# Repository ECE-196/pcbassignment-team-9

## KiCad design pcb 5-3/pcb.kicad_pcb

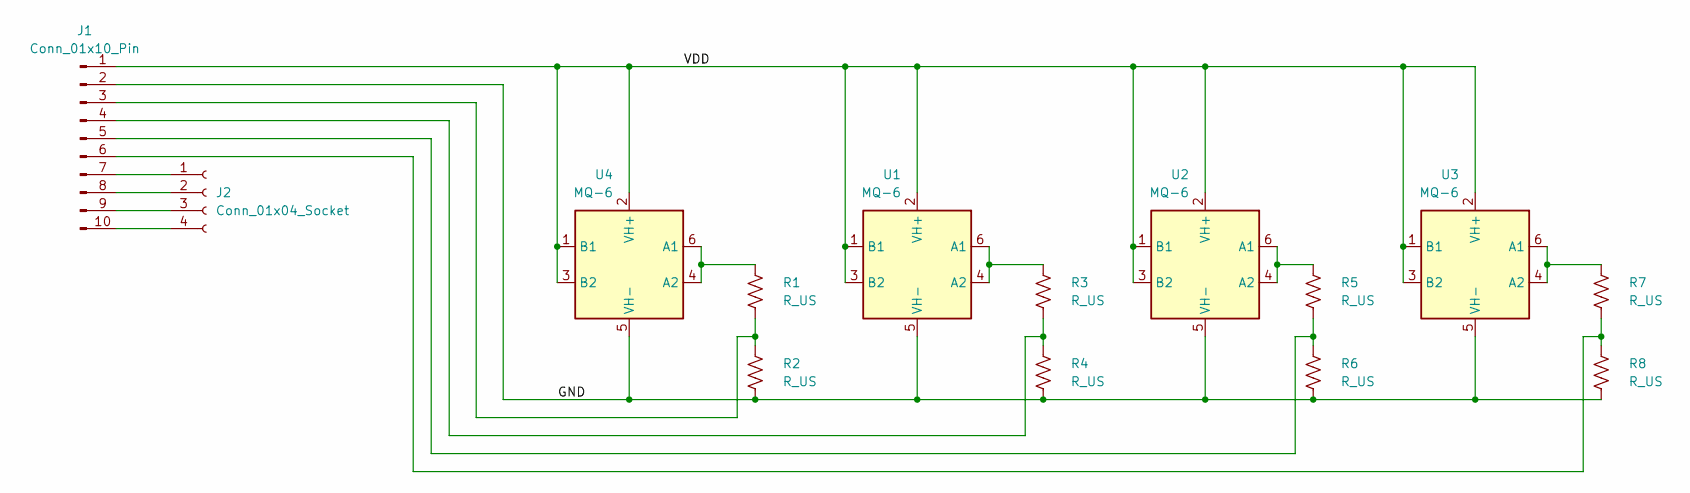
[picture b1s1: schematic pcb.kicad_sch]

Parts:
J1: Conn_01x10_Pin; PinHeader_1x10_P2.54mm_Vertical
J2: Conn_01x04_Socket; PinHeader_1x04_P2.54mm_Vertical
R1, R2, R3, R4, R5, R6, R7, R8: R_US; R_0805_2012Metric
U1, U2, U3, U4: MQ-6

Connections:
/GND: J1.2, R2.2, R4.2, R6.2, R8.2, U1.5 (VH-), U2.5 (VH-), U3.5 (VH-), U4.5 (VH-)
/VDD: J1.1, U1.1 (B1), U1.2 (VH+), U1.3 (B2), U2.1 (B1), U2.2 (VH+), U2.3 (B2), U3.1 (B1), U3.2 (VH+), U3.3 (B2), U4.1 (B1), U4.2 (VH+), U4.3 (B2)
unnamed: J1.3, R1.2, R2.1
unnamed: J1.4, R3.2, R4.1
unnamed: J1.5, R5.2, R6.1
unnamed: J1.6, R7.2, R8.1
unnamed: J1.7, J2.1
unnamed: J1.8, J2.2
unnamed: J1.9, J2.3
unnamed: J1.10, J2.4
unnamed: R3.1, U1.4 (A2), U1.6 (A1)
unnamed: R5.1, U2.4 (A2), U2.6 (A1)
unnamed: R7.1, U3.4 (A2), U3.6 (A1)
unnamed: R1.1, U4.4 (A2), U4.6 (A1)

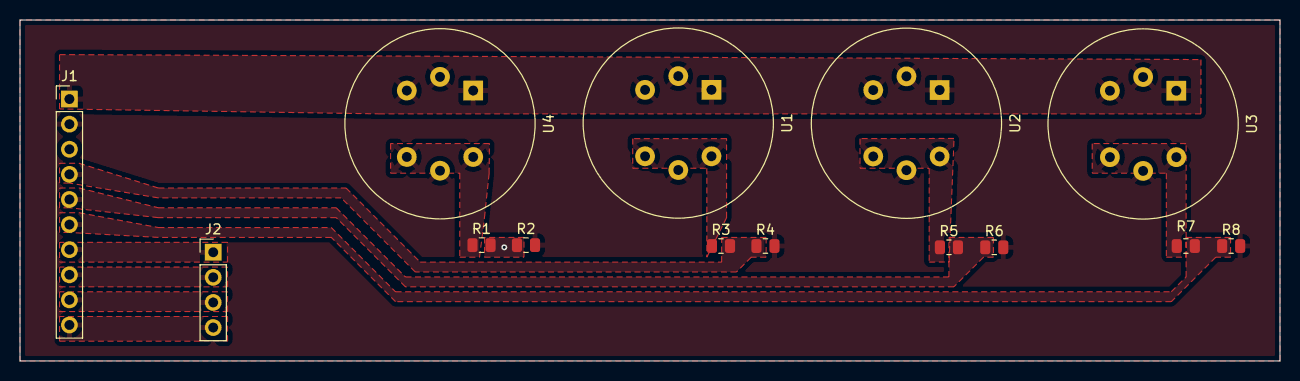
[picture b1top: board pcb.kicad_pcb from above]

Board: 2 copper layers, 127.5 x 34.5 mm, 14 parts (0 on the bottom side), 14 nets.

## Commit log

2024-04-28 add deadline
2024-04-29 Added First Draft Schematic
2024-05-01 Added 4/30 submission
2024-05-04 added final schematic and final kiCAD file called 'pcb 5-3'
2024-05-04 Fixed "PCB Fixes (URGENT) #1"
